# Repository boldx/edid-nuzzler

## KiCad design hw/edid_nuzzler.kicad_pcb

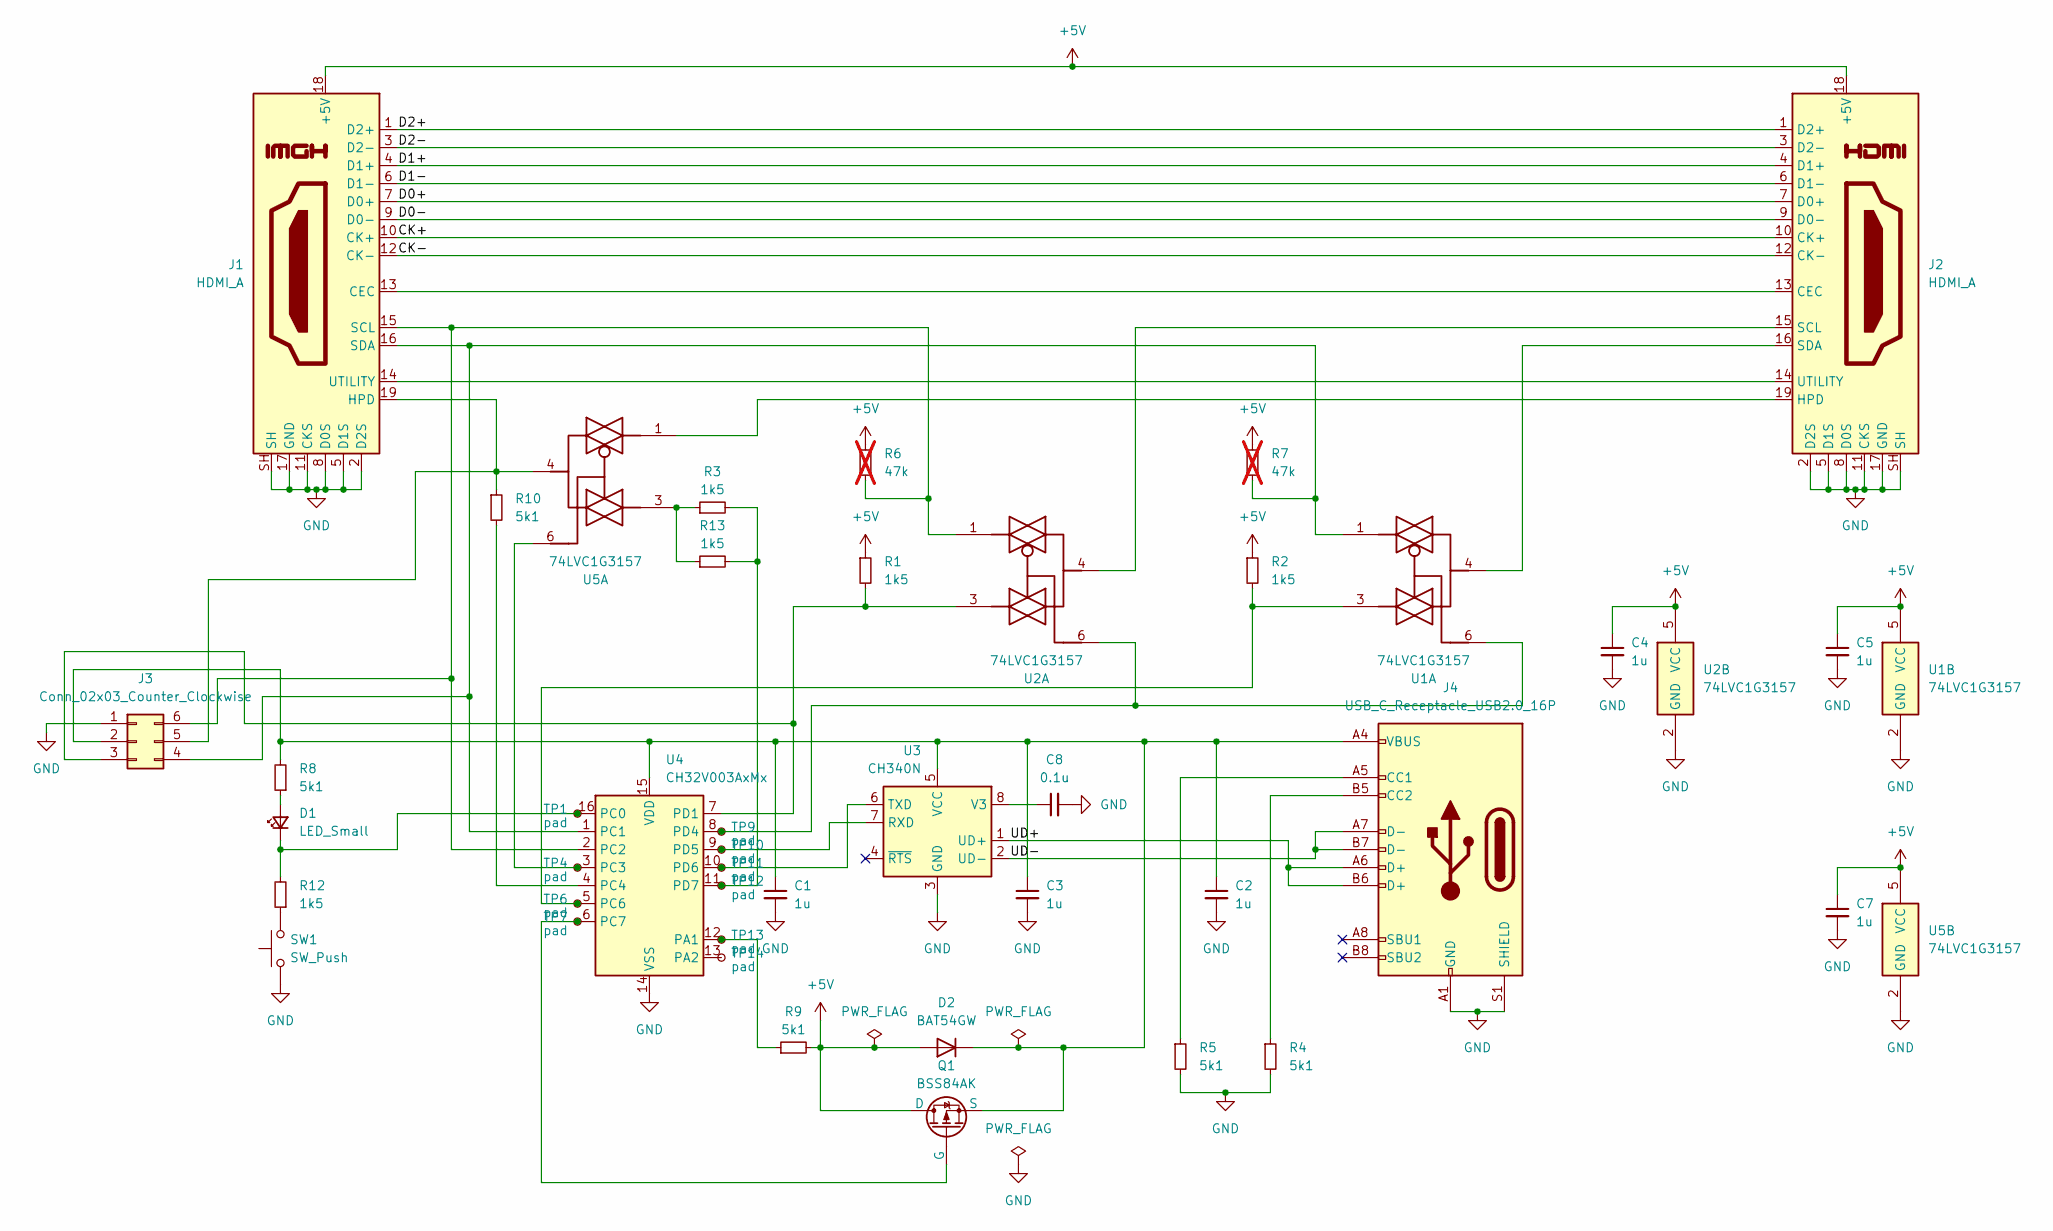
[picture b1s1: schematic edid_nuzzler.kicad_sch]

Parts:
C1, C2, C3, C4, C5, C7: 1u; C_0603_1608Metric_Pad1.08x0.95mm_HandSolder
C8: 0.1u; C_0603_1608Metric_Pad1.08x0.95mm_HandSolder
D1: LED_Small; LED_0603_1608Metric_Pad1.05x0.95mm_HandSolder
D2: BAT54GW; D_SOD-123
J1, J2: HDMI_A; HDMI_A_Molex_208658-1001_Horizontal
J3: Conn_02x03_Counter_Clockwise; PinHeader_2x03_P2.54mm_Vertical
J4: USB_C_Receptacle_USB2.0_16P; USB_C_Receptacle_G-Switch_GT-USB-7010ASV
Q1: BSS84AK; SOT-23
R1, R2, R3, R12, R13: 1k5; R_0603_1608Metric_Pad0.98x0.95mm_HandSolder
R4, R5, R8, R9, R10: 5k1; R_0603_1608Metric_Pad0.98x0.95mm_HandSolder
R6, R7: 47k; R_0603_1608Metric_Pad0.98x0.95mm_HandSolder; not fitted
SW1: SW_Push; SW_XKB_TS-1101-C-W
TP1, TP4, TP6, TP7, TP9, TP10, TP11, TP12, TP13, TP14: pad; TestPoint_Pad_D1.0mm
U1, U2, U5: 74LVC1G3157; SOT-363_SC-70-6_Handsoldering
U3: CH340N; SOP-8_3.9x4.9mm_P1.27mm
U4: CH32V003AxMx; SOP-16_3.9x9.9mm_P1.27mm

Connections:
+5V: C4.1, C5.1, C7.1, D2.2 (A), J1.18 (+5V), J2.18 (+5V), Q1.1 (D), R1.1, R2.1, R6.1, R7.1, R9.2, U1.5 (VCC), U2.5 (VCC), U5.5 (VCC)
/CK+: J1.10 (CK+), J2.10 (CK+)
/CK-: J1.12 (CK-), J2.12 (CK-)
/D0+: J1.7 (D0+), J2.7 (D0+)
/D0-: J1.9 (D0-), J2.9 (D0-)
/D1+: J1.4 (D1+), J2.4 (D1+)
/D1-: J1.6 (D1-), J2.6 (D1-)
/D2+: J1.1 (D2+), J2.1 (D2+)
/D2-: J1.3 (D2-), J2.3 (D2-)
/UD+: J4.A6 (D+), J4.B6 (D+), U3.1 (UD+)
/UD-: J4.A7 (D-), J4.B7 (D-), U3.2 (UD-)
GND: C1.2, C2.2, C3.2, C4.2, C5.2, C7.2, C8.2, J1.2 (D2S), J1.5 (D1S), J1.8 (D0S), J1.11 (CKS), J1.17 (GND), J1.SH, J2.2 (D2S), J2.5 (D1S), J2.8 (D0S), J2.11 (CKS), J2.17 (GND), J2.SH, J3.1, J4.A1 (GND), J4.A12 (GND), J4.B1 (GND), J4.B12 (GND), J4.S1 (SHIELD), R4.2, R5.2, SW1.1, U1.2 (GND), U2.2 (GND), U3.3 (GND), U4.14 (VSS), U5.2 (GND)
unnamed: D1.2 (A), R8.1
unnamed: D1.1 (K), R12.2, TP1.1, U4.16 (PC0)
unnamed: C1.1, C2.1, C3.1, D2.1 (K), J3.2, J4.A4 (VBUS), J4.A9 (VBUS), J4.B4 (VBUS), J4.B9 (VBUS), Q1.3 (S), R8.2, U3.5 (VCC), U4.15 (VDD)
unnamed: J1.13 (CEC), J2.13 (CEC)
unnamed: J1.19 (HPD), J3.5, R10.1, U5.4
unnamed: J1.15 (SCL), J3.6, R6.2, U2.1, U4.2 (PC2)
unnamed: J1.16 (SDA), J3.4, R7.2, U1.1, U4.1 (PC1)
unnamed: J1.14 (UTILITY), J2.14 (UTILITY)
unnamed: J2.19 (HPD), U5.1
unnamed: J2.15 (SCL), U2.4
unnamed: J2.16 (SDA), U1.4
unnamed: J3.3, R1.2, U2.3, U4.7 (PD1)
unnamed: J4.A5 (CC1), R5.1
unnamed: J4.B5 (CC2), R4.1
unnamed: Q1.2 (G), TP7.1, U4.6 (PC7)
unnamed: R12.1, SW1.2
unnamed: R3.1, R13.1, U5.3
unnamed: TP10.1, U3.7 (RXD), U4.9 (PD5)
unnamed: TP11.1, U3.6 (TXD), U4.10 (PD6)
unnamed: C8.1, U3.8 (V3)
unnamed: R9.1, TP13.1, U4.12 (PA1)
unnamed: TP14.1, U4.13 (PA2)
unnamed: TP4.1, U4.3 (PC3), U5.6
unnamed: R10.2, U4.4 (PC4)
unnamed: R2.2, TP6.1, U1.3, U4.5 (PC6)
unnamed: TP9.1, U1.6, U2.6, U4.8 (PD4)
unnamed: R3.2, R13.2, TP12.1, U4.11 (PD7)

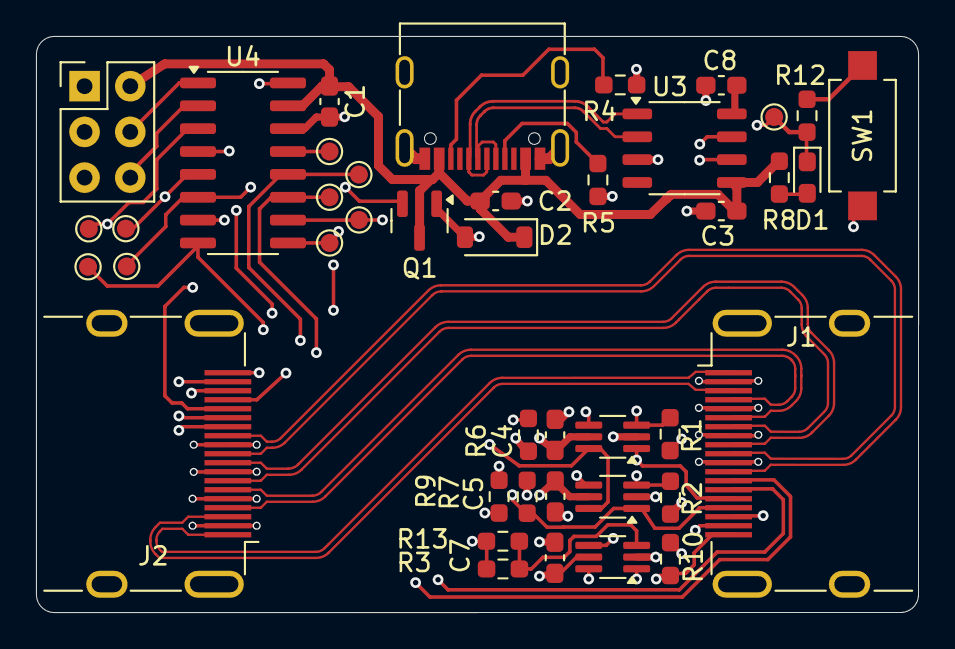
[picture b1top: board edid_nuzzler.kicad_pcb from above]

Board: 4 copper layers, 49.0 x 32.0 mm, 42 parts (0 on the bottom side), 39 nets.

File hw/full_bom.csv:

"Reference","Value","Datasheet","Footprint","Qty","DNP"
"C1,C2,C3,C4,C5,C7","1u","~","Capacitor_SMD:C_0603_1608Metric_Pad1.08x0.95mm_HandSolder","6",""
"C8","0.1u","~","Capacitor_SMD:C_0603_1608Metric_Pad1.08x0.95mm_HandSolder","1",""
"D1","LED_Small","~","LED_SMD:LED_0603_1608Metric_Pad1.05x0.95mm_HandSolder","1",""
"D2","BAT54GW","~","Diode_SMD:D_SOD-123","1",""
"J1,J2","HDMI_A","https://en.wikipedia.org/wiki/HDMI","Connector_Video:HDMI_A_Molex_208658-1001_Horizontal","2",""
"J3","Conn_02x03_Counter_Clockwise","~","Connector_PinHeader_2.54mm:PinHeader_2x03_P2.54mm_Vertical","1",""
"J4","USB_C_Receptacle_USB2.0_16P","https://www.usb.org/sites/default/files/documents/usb_type-c.zip","Connector_USB:USB_C_Receptacle_G-Switch_GT-USB-7010ASV","1",""
"Q1","BSS84AK","https://ngspice.sourceforge.io/docs/ngspice-html-manual/manu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","Package_TO_SOT_SMD:SOT-23","1",""
"R1,R2,R3,R12,R13","1k5","~","Resistor_SMD:R_0603_1608Metric_Pad0.98x0.95mm_HandSolder","5",""
"R4,R5,R8,R9,R10","5k1","~","Resistor_SMD:R_0603_1608Metric_Pad0.98x0.95mm_HandSolder","5",""
"R6,R7","47k","~","Resistor_SMD:R_0603_1608Metric_Pad0.98x0.95mm_HandSolder","2","DNP"
"SW1","SW_Push","~","nuzzler:SW_XKB_TS-1101-C-W","1",""
"TP1,TP4,TP6,TP7,TP9,TP10,TP11,TP12,TP13,TP14","pad","~","TestPoint:TestPoint_Pad_D1.0mm","10",""
"U1,U2,U5","74LVC1G3157","http://www.ti.com/lit/sg/scyt129e/scyt129e.pdf","Package_TO_SOT_SMD:SOT-363_SC-70-6_Handsoldering","3",""
"U3","CH340N","https://aitendo3.sakura.ne.jp/aitendo_data/product_img/ic/in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","Package_SO:SOP-8_3.9x4.9mm_P1.27mm","1",""
"U4","CH32V003AxMx","https://www.wch-ic.com/products/CH32V003.html","Package_SO:SOP-16_3.9x9.9mm_P1.27mm","1",""

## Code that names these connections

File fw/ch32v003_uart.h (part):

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 * 
 *	USART1 mapping configuration high (used in conjunction with AFIO PCFR1 register bit2
 *	USART1RM [21,2]).
 * 	00: default mapping (CK/PD4, TX/PD5, RX/PD6, CTS/PD3, RTS/PC2, SW_RX/PD5).
 *	01: Remapping (CK/PD7, TX/PD0, RX/PD1, CTS/PC3, RTS/PC2, SW_RX/PD0).
 *	10: Remapping (CK/PD7, TX/PD6, RX/PD5, CTS/PC6, RTS/PC7, SW_RX/PD6).
 *	11: Remapping (CK/PC5, TX/PC0, RX/PC1, CTS/PC6, RTS/PC7, SW_RX/PC0).
 *
 * Usage:
 * 1. In funconfig.h define the baudrate:
 *    #define FUNCONF_UART_PRINTF_BAUD 115200 //used for uart library
 * 
 * 2. In main source file: optionally define the TXRX pin configuration. If not defined
 *    the standard TX=PD5, RX=PD6 is used, alternative settings:
 *    #define UART_PINS_TXPD0_RXPD1 or
 *    #define UART_PINS_TXPC0_RXPC1 or
 *    #define UART_PINS_TXPD6_RXPD5 - this is the TXRX swap setting
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
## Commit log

2025-05-23 first!
2025-05-24 Corase layout
2025-05-25 Hopefully better high speed layout
2025-06-01 PCB wip
2025-06-01 ignore autsave
2025-06-01 Rough idea about routing
2025-06-01 trace cleanup
2025-06-07 Mostly done
2025-06-19 v1.0 HW as sent to fab
2025-06-23 Sync J3 sch symbol numbering order with the pcb footprint
2025-06-23 PoC firmware
2025-07-05 Basic operations: get/set/store EDID data, get/set HPD pin state
